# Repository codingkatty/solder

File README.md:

# or gate pcb
hi i'm @Candy and this is my pcb made for [solder](https://solder.hackclub.com/) :3, here are some images:

### Description

this pcb is cat themed and its function is an 'or gate', where any button pressed will trigger the led and mini motor disc. i spent some time learning and trying to make circuits with [this^](https://www.falstad.com/circuit/circuitjs.html) and i made this cool circuit!

### Bill of Materials
| Item | Quantity |
| --- | --- |
| Resistors (220Ω) | 4 |
| Push button | 2 |
| 2N3904 transistors | 2 |
| Battery cell | 1 |
| Potentiometer | 1 |
| Mini motor disc | 1 |
| LED | 1 |

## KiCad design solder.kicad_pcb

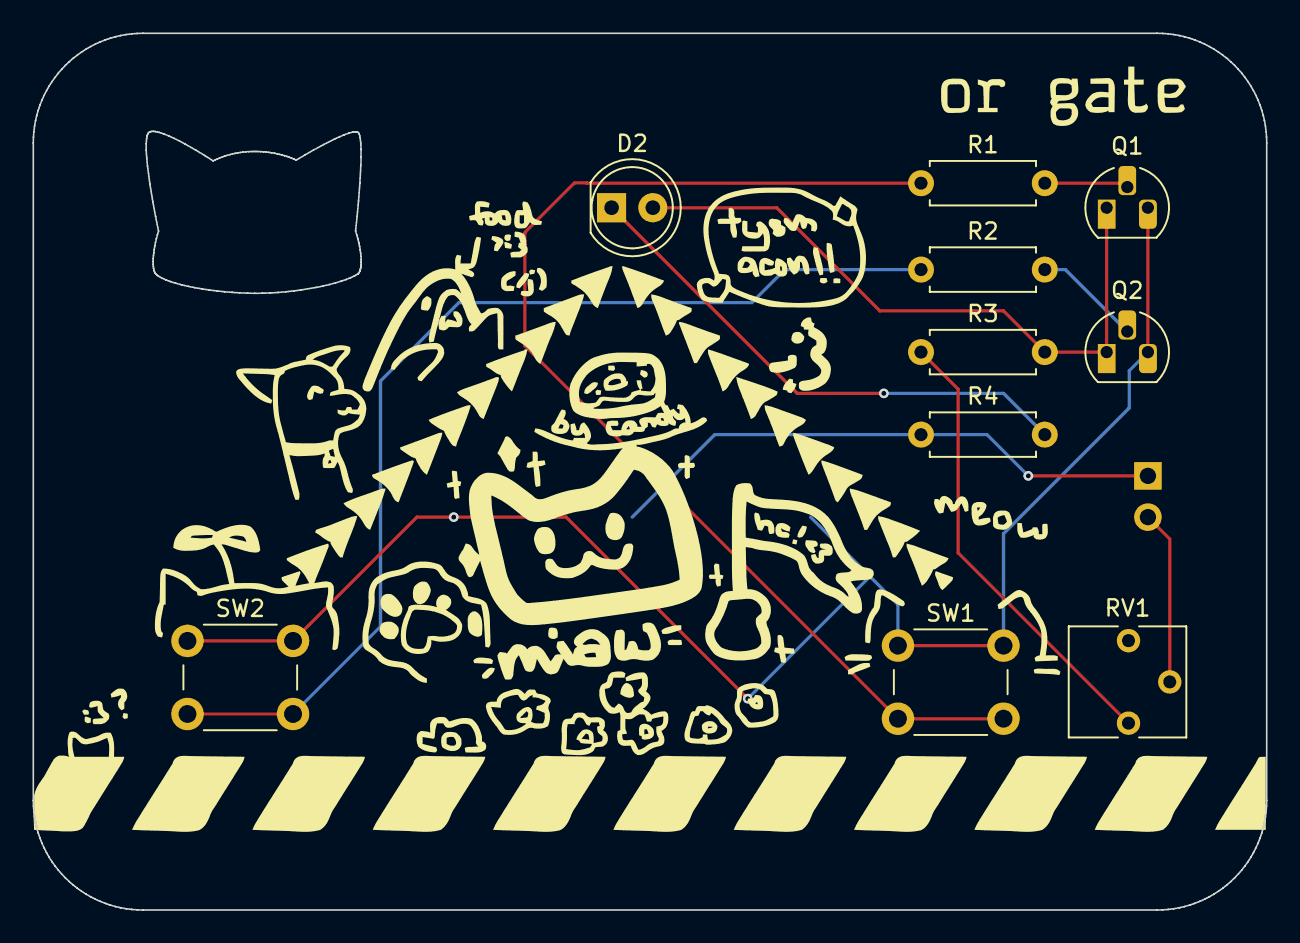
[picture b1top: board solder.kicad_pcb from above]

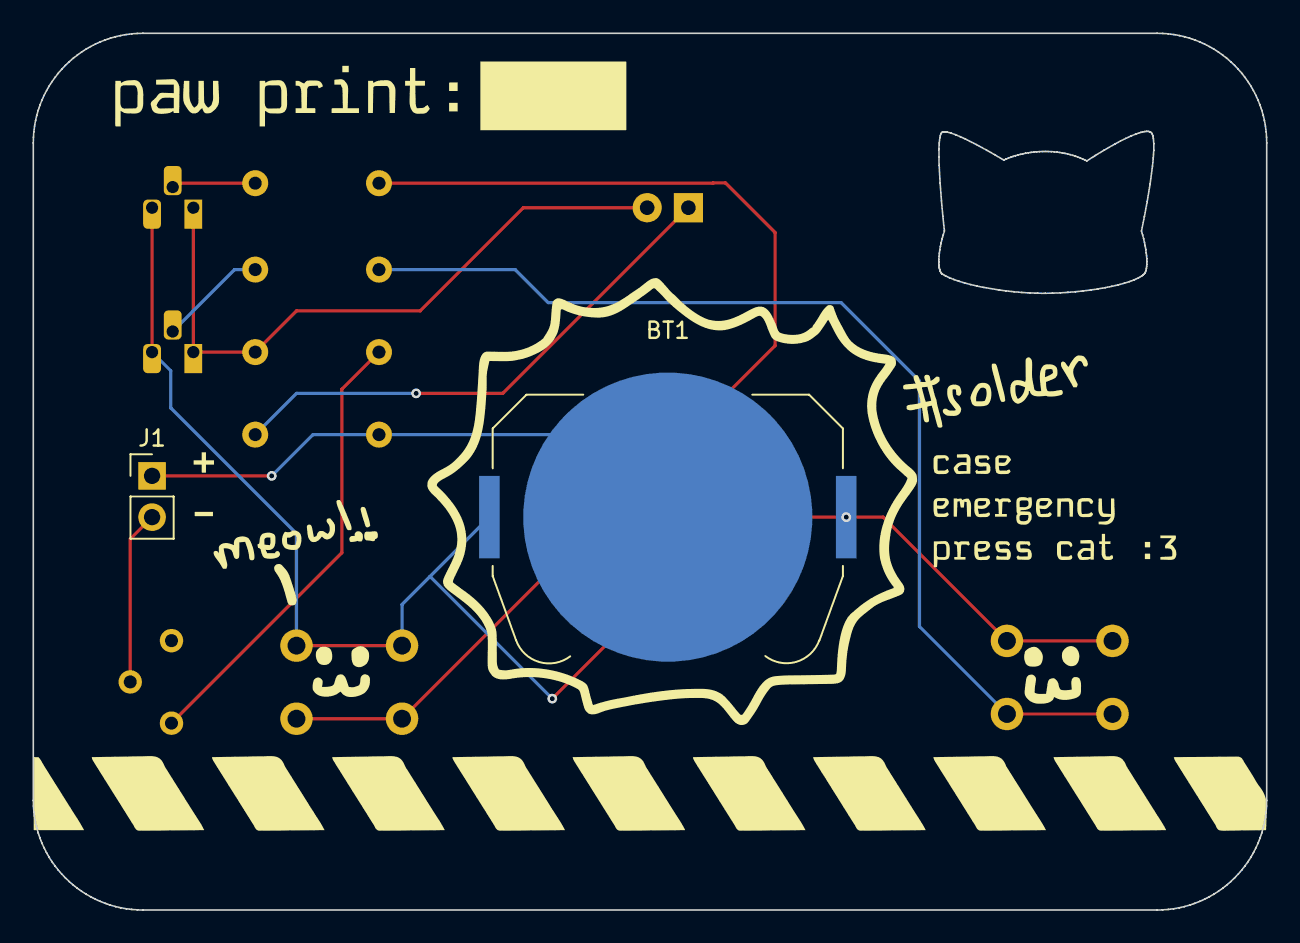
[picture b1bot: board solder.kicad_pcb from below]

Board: 2 copper layers, 75.9 x 54.0 mm, 12 parts (2 on the bottom side), 10 nets.

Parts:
BT1: Battery_Cell; BatteryHolder_Keystone_3034_1x20mm
D2: LED; LED_D5.0mm
J1: Conn_01x02_Pin; PinHeader_1x02_P2.54mm_Vertical
Q1, Q2: 2N3904; TO-92L_HandSolder
R1, R2, R3, R4: R; R_Axial_DIN0207_L6.3mm_D2.5mm_P7.62mm_Horizontal
RV1: R_Potentiometer; Potentiometer_Vishay_T73YP_Vertical
SW1, SW2: SW_Push; SW_PUSH_6mm

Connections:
+3.3V: BT1.1 (+), Q1.3 (C), Q2.3 (C), SW1.1, SW2.1
GND: BT1.2 (-), J1.1, R4.1
unnamed: D2.2 (A), Q1.1 (E), Q2.1 (E), R3.2
unnamed: D2.1 (K), R4.2
unnamed: J1.2, RV1.2
unnamed: Q1.2 (B), R1.2
unnamed: Q2.2 (B), R2.2
unnamed: R1.1, SW1.2
unnamed: R2.1, SW2.2
unnamed: R3.1, RV1.1

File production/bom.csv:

Designator,Footprint,Quantity,Value,LCSC Part #
BT1,BatteryHolder_Keystone_3034_1x20mm,1,Battery_Cell,
D2,LED_D5.0mm,1,LED,
J1,PinHeader_1x02_P2.54mm_Vertical,1,Conn_01x02_Pin,
"Q1, Q2",TO-92L_HandSolder,2,2N3904,
"R1, R2, R3, R4",R_Axial_DIN0207_L6.3mm_D2.5mm_P7.62mm_Horizontal,4,R,
RV1,Potentiometer_Vishay_T73YP_Vertical,1,R_Potentiometer,
"SW1, SW2",SW_PUSH_6mm,2,SW_Push,

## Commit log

2025-06-15 add stuff :3
2025-06-15 add files
2025-06-16 add back silkscreen
